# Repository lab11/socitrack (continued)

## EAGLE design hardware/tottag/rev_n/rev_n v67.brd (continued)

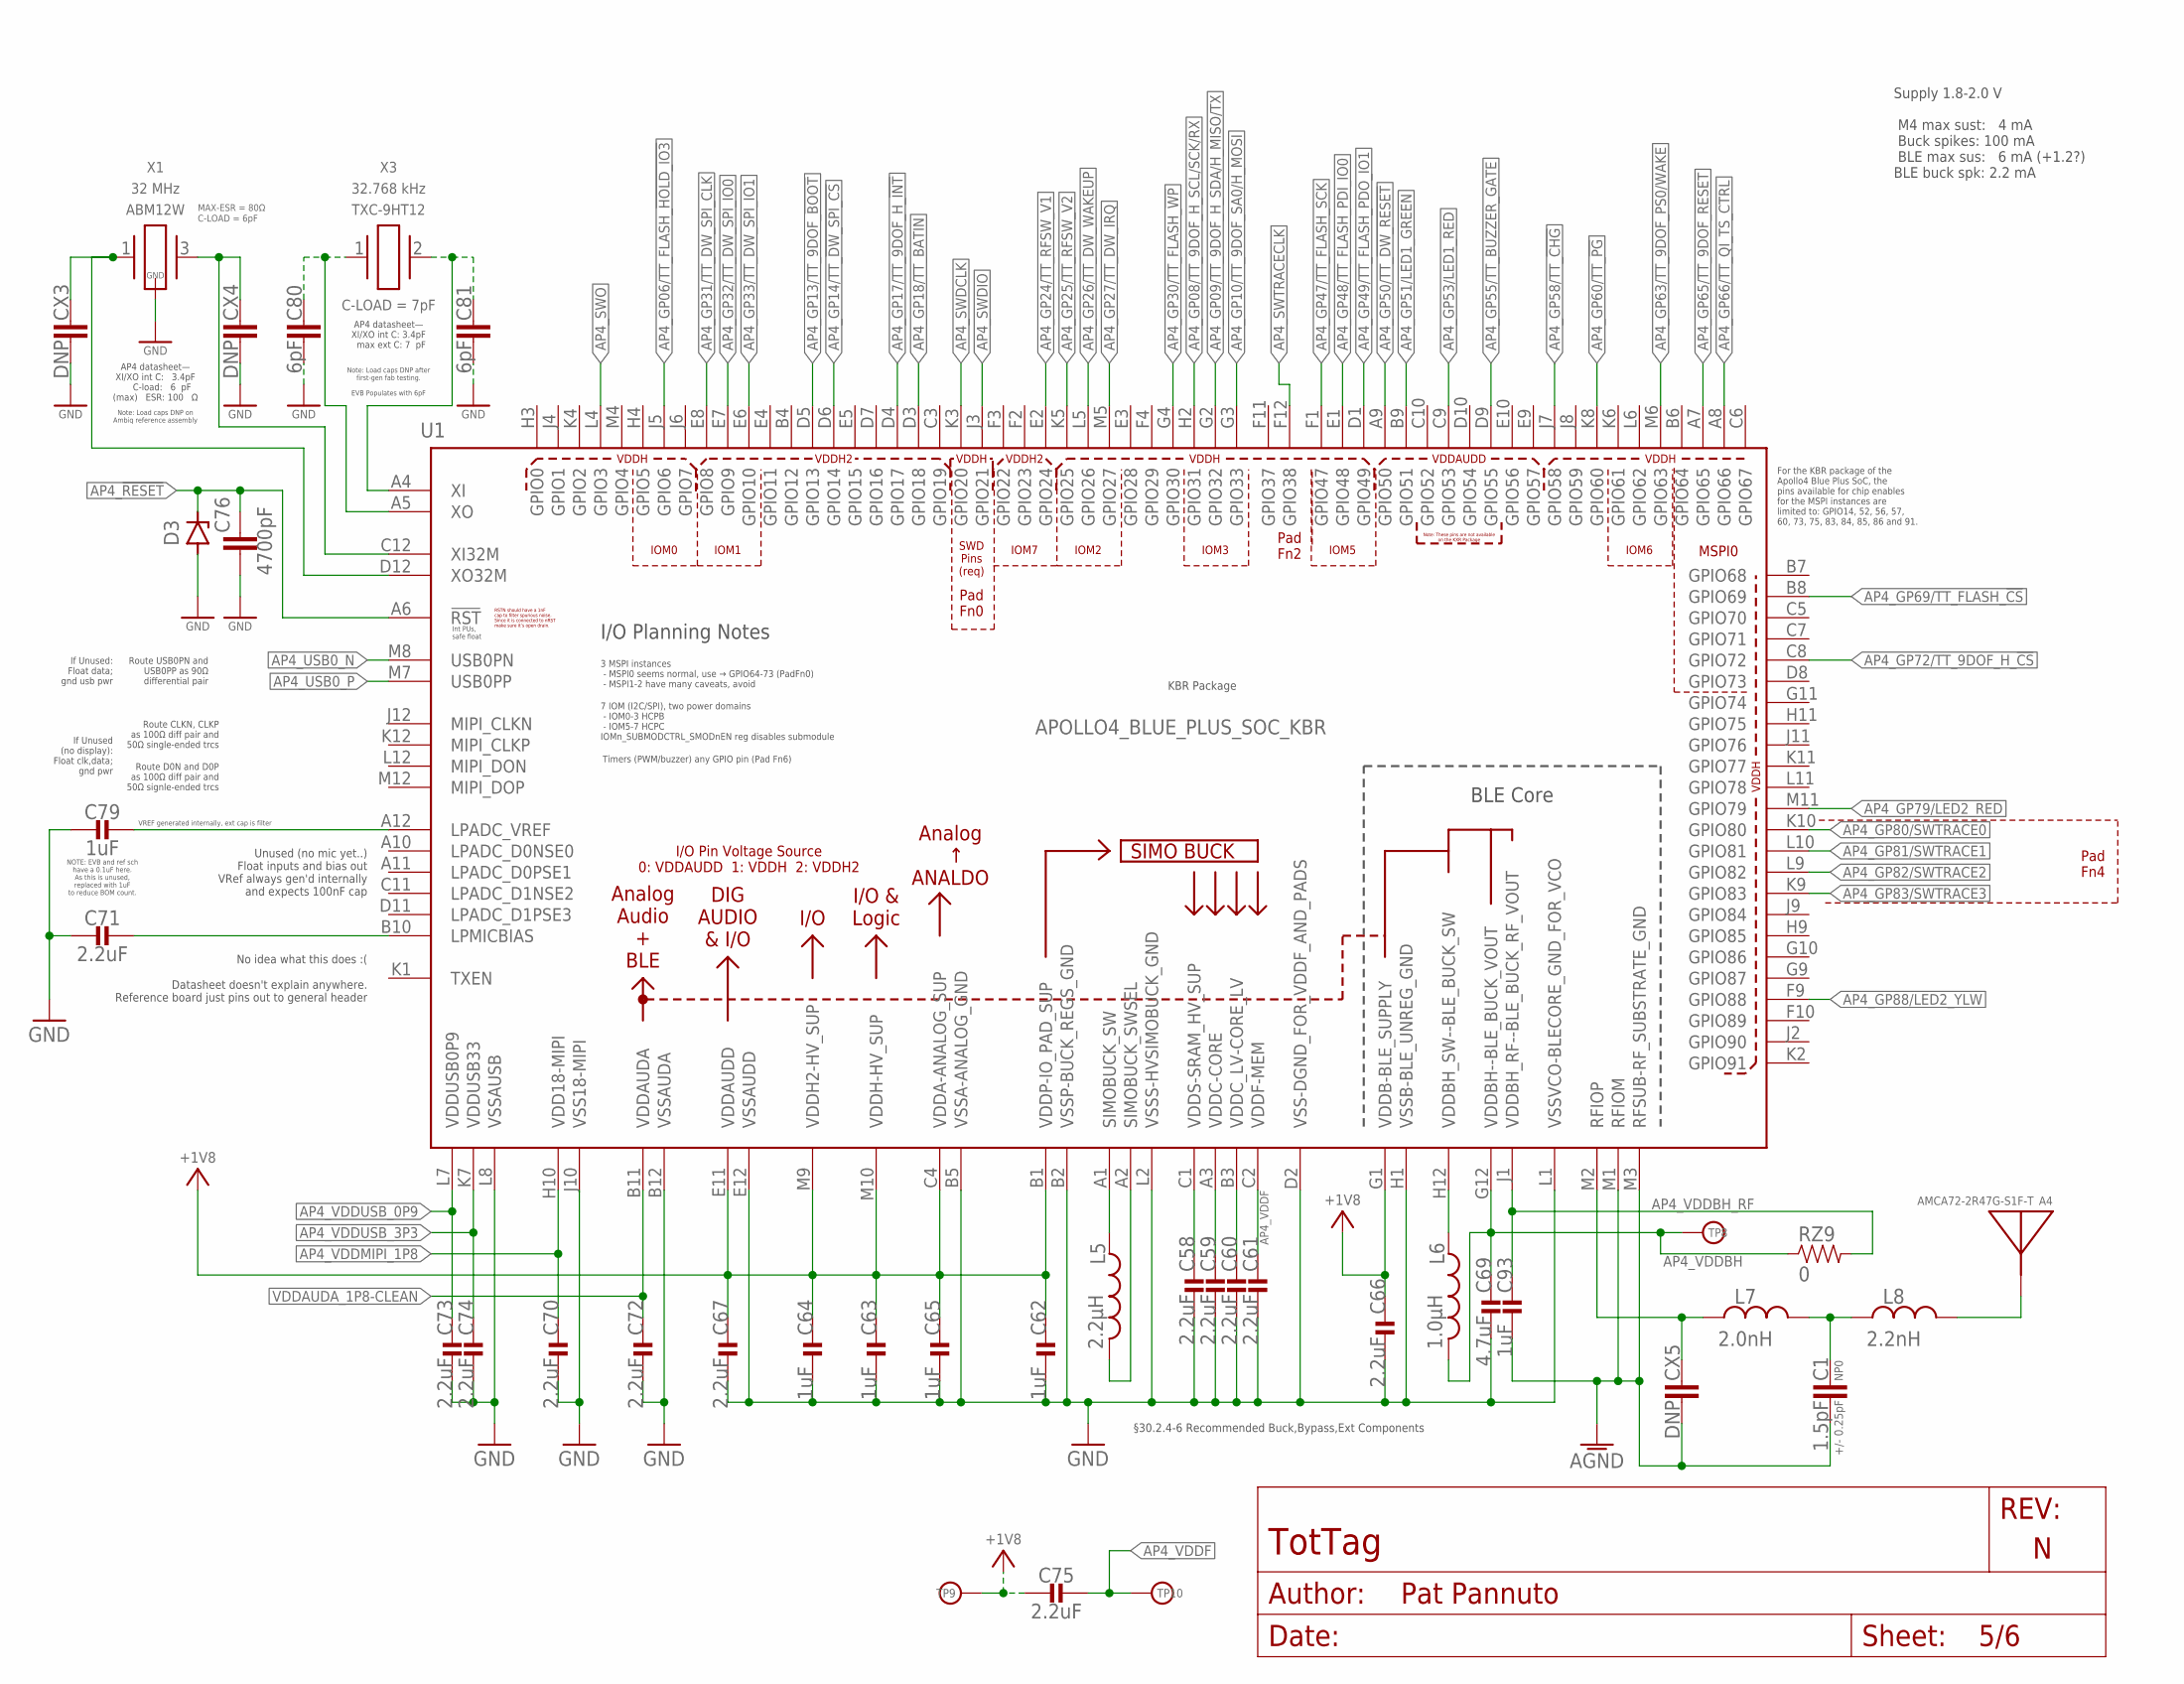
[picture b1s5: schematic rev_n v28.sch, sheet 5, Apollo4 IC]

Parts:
A4: AMCA72-2R47G-S1F-T; AMCA72-2R470G-S1F-T
C1: 1.5pF; CAPC1005X60; TOLERANCE +/- 0.25pF; MPN C0402C159C5GAC7867
C58, C59, C60, C61, C66, C67, C70, C71, C72, C73, C74, C75: 2.2uF; 0201_CAP; MPN GRM033R61A225KE47D
C62, C63, C64, C65, C79, C93: 1uF; 0201_CAP; MPN GRM033R61A105ME44D
C69: 4.7uF; 0402_CAP; MPN CL05A475MP5NRNC
C76: 4700pF; CAPC1005X60; MPN KGM05AR71E472KH
C80, C81: 6pF; CAPC1005X60; MPN GCM1555C1H6R0BA16D
CX3, CX4, CX5: DNP; CAPC1005X60
D3: ZENER; SODFL1608X70; MPN PESD5V0X1UB,135
L5: 2.2µH; 0805_CAP; MPN DFE201210U-2R2M=P2
L6: 1.0µH; 0603_CAP; MPN DFE18SAN1R0ME0L
L7: 2.0nH; INDC1006X60N; TOLERANCE +/- 0.1 nH; MPN CTTF0402F-2N0B
L8: 2.2nH; INDC1006X60N; TOLERANCE +/- 0.1 nH; MPN CTTF0402F-2N2B
RZ9: 0; 0402_RES; MPN RMCF0402ZT0R00
TP8: VDDBH; PAD.03X.03
TP9: VDDP; PAD.03X.03
TP10: VDDF; PAD.03X.03
U1: APOLLO4_BLUE_PLUS_SOC_KBR; APOLLO4_BLUE_SOC_BGA
X1: ABM12W; MPN ABM12W-32.0000MHZ-6-D1X-T3
X3: TXC-9HT12; MPN 9HT12-32.768KDZY-T

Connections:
AGND: C1.2, C93.P$2 (2), CX5.2, U1.M1 (RFIOM), U1.M3 (RFSUB-RF_SUBSTRATE_GND)
AP4_!RESET: C76.1, D3.1 (C), U1.A6 (!RST); also elsewhere on the board
AP4_GP06/TT_FLASH_!HOLD_IO3: U1.J5 (GPIO6); also elsewhere on the board
AP4_GP08/TT_9DOF_H_SCL/SCK/RX: U1.H2 (GPIO31); also elsewhere on the board
AP4_GP13/TT_9DOF_!BOOT: U1.D5 (GPIO13); also elsewhere on the board
AP4_GP14/TT_!DW_SPI_CS: U1.D6 (GPIO14); also elsewhere on the board
AP4_GP17/TT_9DOF_H_!INT: U1.D4 (GPIO17); also elsewhere on the board
AP4_GP18/TT_BATIN: U1.D3 (GPIO18); also elsewhere on the board
AP4_GP24/TT_RFSW_V1: U1.E2 (GPIO24); also elsewhere on the board
AP4_GP25/TT_RFSW_V2: U1.K5 (GPIO25); also elsewhere on the board
AP4_GP26/TT_DW_WAKEUP: U1.L5 (GPIO26); also elsewhere on the board
AP4_GP27/TT_DW_IRQ: U1.M5 (GPIO27); also elsewhere on the board
AP4_GP30/TT_FLASH_!WP: U1.G4 (GPIO30); also elsewhere on the board
AP4_GP31/TT_DW_SPI_CLK: U1.E8 (GPIO8); also elsewhere on the board
AP4_GP32/TT_DW_SPI_IO0: U1.E7 (GPIO9); also elsewhere on the board
AP4_GP33/TT_DW_SPI_IO1: U1.E6 (GPIO10); also elsewhere on the board
AP4_GP47/TT_FLASH_SCK: U1.F1 (GPIO47); also elsewhere on the board
AP4_GP48/TT_FLASH_PDI_IO0: U1.E1 (GPIO48); also elsewhere on the board
AP4_GP49/TT_FLASH_PDO_IO1: U1.D1 (GPIO49); also elsewhere on the board
AP4_GP50/TT_!DW_RESET: U1.A9 (GPIO50); also elsewhere on the board
AP4_GP51/LED1_GREEN: U1.B9 (GPIO51); also elsewhere on the board
AP4_GP53/LED1_RED: U1.C9 (GPIO53); also elsewhere on the board
AP4_GP55/TT_BUZZER_GATE: U1.D9 (GPIO55); also elsewhere on the board
AP4_GP58/TT_!CHG: U1.J7 (GPIO58); also elsewhere on the board
AP4_GP60/TT_!PG: U1.K8 (GPIO60); also elsewhere on the board
AP4_GP63/TT_9DOF_PS0/WAKE: U1.M6 (GPIO63); also elsewhere on the board
AP4_GP65/TT_9DOF_!RESET: U1.A7 (GPIO65); also elsewhere on the board
AP4_GP66/TT_QI_TS_CTRL: U1.A8 (GPIO66); also elsewhere on the board
AP4_GP69/TT_FLASH_!CS: U1.B8 (GPIO69); also elsewhere on the board
AP4_GP72/TT_9DOF_H_!CS: U1.C8 (GPIO72); also elsewhere on the board
AP4_GP79/LED2_RED: U1.M11 (GPIO79); also elsewhere on the board
AP4_GP88/LED2_YLW: U1.F9 (GPIO88); also elsewhere on the board
AP4_LPADC_VREF: C79.P$2 (2), U1.A12 (LPADC_VREF)
AP4_LPMICBIAS: C71.P$2 (2), U1.B10 (LPMICBIAS)
AP4_RFIOP1: CX5.1, L7.1, U1.M2 (RFIOP)
AP4_SWDCLK: U1.K3 (GPIO20); also elsewhere on the board
AP4_SWDIO: U1.J3 (GPIO21); also elsewhere on the board
AP4_SWO: U1.L4 (GPIO3); also elsewhere on the board
AP4_USB0_N: U1.M8 (USB0PN)
AP4_USB0_P: U1.M7 (USB0PP)
AP4_VDDBH: C69.1, L6.2, RZ9.1, TP8.P$1, U1.G12 (VDDBH--BLE_BUCK_VOUT)
AP4_VDDBH_RF: C93.P$1 (1), RZ9.2, U1.J1 (VDDBH_RF--BLE_BUCK_RF_VOUT)
AP4_VDDBH_SW: L6.1, U1.H12 (VDDBH_SW--BLE_BUCK_SW)
AP4_VDDC: C59.P$1 (1), U1.A3 (VDDC-CORE)
AP4_VDDC_LV: C60.P$1 (1), U1.B3 (VDDC_LV-CORE_LV)
AP4_VDDF: C61.P$1 (1), C75.P$1 (1), TP10.P$1, U1.C2 (VDDF-MEM)
AP4_VDDMIPI_1P8: C70.P$1 (1), U1.H10 (VDD18-MIPI); also elsewhere on the board
AP4_VDDS: C58.P$1 (1), U1.C1 (VDDS-SRAM_HV_SUP)
AP4_VDDUSB_0P9: C73.P$1 (1), U1.L7 (VDDUSB0P9); also elsewhere on the board
AP4_VDDUSB_3P3: C74.P$1 (1), U1.K7 (VDDUSB33); also elsewhere on the board
AP4_XI: C81.1, U1.A4 (XI), X3.2
AP4_XI32M: CX4.1, U1.C12 (XI32M), X1.3 (2)
AP4_XO: C80.1, U1.A5 (XO), X3.1
AP4_XO32M: CX3.1, U1.D12 (XO32M), X1.1
BLE_RFOUT: A4.S1, L8.2
GND: C58.P$2 (2), C59.P$2 (2), C60.P$2 (2), C61.P$2 (2), C62.P$2 (2), C63.P$2 (2), C64.P$2 (2), C65.P$2 (2), C66.P$2 (2), C67.P$2 (2), C69.2, C70.P$2 (2), C71.P$1 (1), C72.P$2 (2), C73.P$2 (2), C74.P$2 (2), C76.2, C79.P$1 (1), C80.2, C81.2, CX3.2, CX4.2, D3.2 (A), U1.B2 (VSSP-BUCK_REGS_GND), U1.B5 (VSSA-ANALOG_GND), U1.B12 (VSSAUDA), U1.D2 (VSS-DGND_FOR_VDDF_AND_PADS), U1.E12 (VSSAUDD), U1.H1 (VSSB-BLE_UNREG_GND), U1.J10 (VSS18-MIPI), U1.L1 (VSSVCO-BLECORE_GND_FOR_VCO), U1.L2 (VSSS-HVSIMOBUCK_GND), U1.L8 (VSSAUSB), X1.2 (GND), X1.4 (GND); also elsewhere on the board
unnamed: C1.1, L7.2, L8.1
SIMOBUCK_SW: L5.P$1 (1), U1.A1 (SIMOBUCK_SW)
SIMOBUCK_SWSEL: L5.P$2 (2), U1.A2 (SIMOBUCK_SWSEL)
VDDAUDA_1P8-CLEAN: C72.P$1 (1), U1.B11 (VDDAUDA); also elsewhere on the board

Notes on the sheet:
Supply 1.8-2.0 V M4 max sust: 4 mA Buck spikes: 100 mA BLE max sus: 6 mA (+1.2?) BLE buck spk: 2.2 mA
Note: Load caps DNP on Ambiq reference assembly
Int PUs, safe float
If Unused: Float data; gnd usb pwr
If Unused (no display): Float clk,data; gnd pwr
Unused (no mic yet..) Float inputs and bias out VRef always gen'd internally and expects 100nF cap
No idea what this does :( Datasheet doesn't explain anywhere. Reference board just pins out to general header
I/O Planning Notes
3 MSPI instances - MSPI0 seems normal, use → GPIO64-73 (PadFn0) - MSPI1-2 have many caveats, avoid
7 IOM (I2C/SPI), two power domains - IOM0-3 HCPB - IOM5-7 HCPC IOMn_SUBMODCTRL_SMODnEN reg disables submodule
MSPI0
IOM0
IOM1
Timers (PWM/buzzer) any GPIO pin (Pad Fn6)
KBR Package
For the KBR package of the Apollo4 Blue Plus SoC, the pins available for chip enables for the MSPI instances are limited to: GPIO14, 52, 56, 57, 60, 73, 75, 83, 84, 85, 86 and 91.
§30.2.4-6 Recommended Buck,Bypass,Ext Components
SWD Pins (req)
VREF generated internally, ext cap is filter
IOM3
AP4 datasheet— XI/XO int C: 3.4pF max ext C: 7 pF
AP4 datasheet— XI/XO int C: 3.4pF C-load: 6 pF (max) ESR: 100 Ω
Pad Fn4
Pad Fn2
Pad Fn0
Note: Load caps DNP after first-gen fab testing. EVB Populates with 6pF
Route USB0PN and USB0PP as 90Ω differential pair
Route CLKN, CLKP as 100Ω diff pair and 50Ω single-ended trcs
Route D0N and D0P as 100Ω diff pair and 50Ω signle-ended trcs
NOTE: EVB and ref sch have a 0.1uF here. As this is unused, replaced with 1uF to reduce BOM count.
IOM2
IOM5
IOM6
IOM7

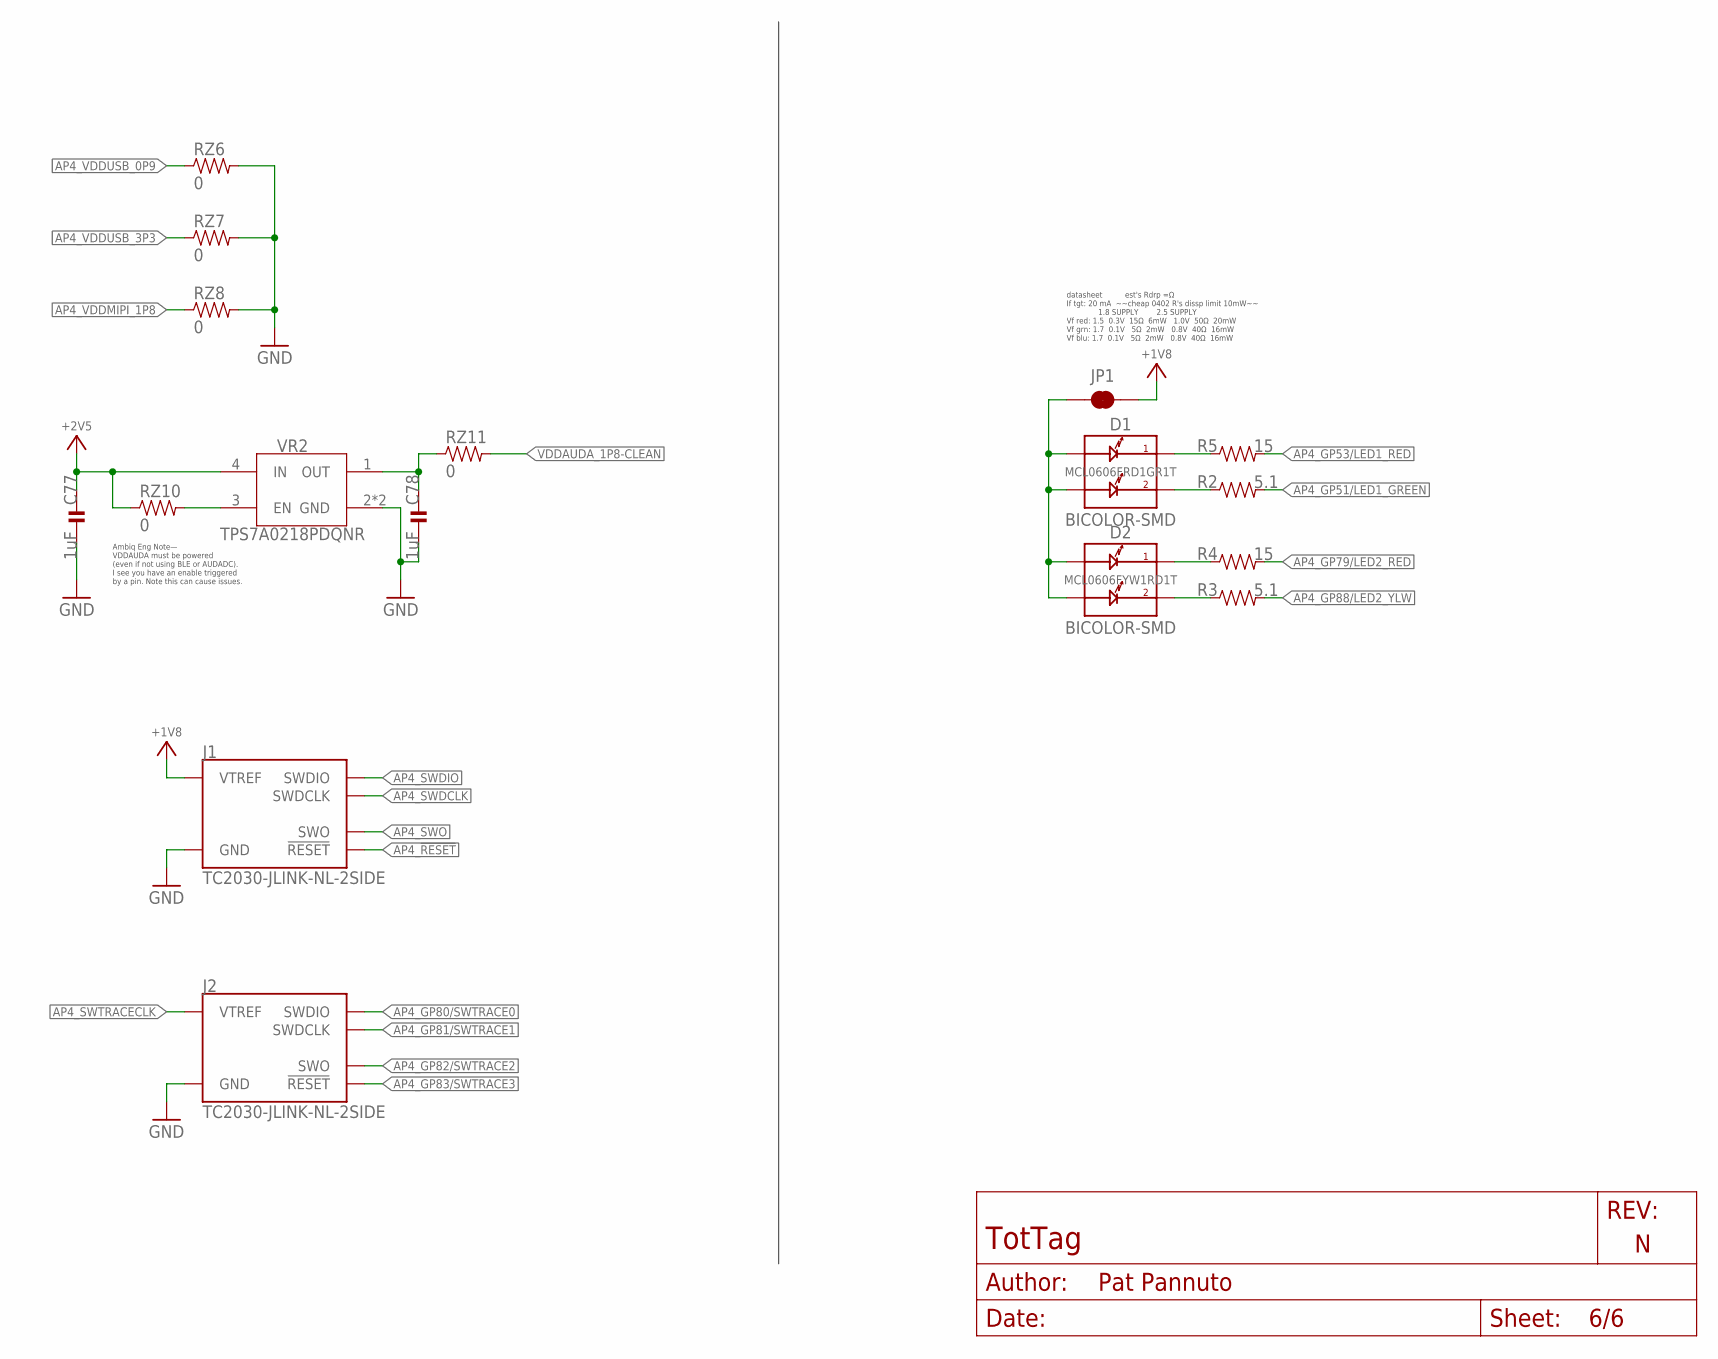
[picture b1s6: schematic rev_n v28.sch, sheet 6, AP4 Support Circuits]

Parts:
C77, C78: 1uF; 0201_CAP; MPN GRM033R61A105ME44D
D1: BICOLOR-SMD; LED-0606; MPN MCL0606FRD1GR1T
D2: BICOLOR-SMD; LED-0606; MPN MCL0606FYW1RD1T
J1, J2: TC2030-JLINK-NL-2SIDE; TC2030-IDC-NL-2SIDE
JP1: JUMPER-SMT_2_NC_TRACE_SILK; SMT-JUMPER_2_NC_TRACE_SILK
R2, R3: 5.1; 0402_RES; MPN RC0402JR-075R1L
R4, R5: 15; 0402_RES; MPN RC0402JR-0715RL
RZ6, RZ7, RZ8, RZ10, RZ11: 0; 0402_RES; MPN RMCF0402ZT0R00
VR2: TPS7A0218PDQNR; 4-XDFN-EP

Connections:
+2V5: C77.P$1 (1), RZ10.1, VR2.4 (IN); also elsewhere on the board
AP4_!RESET: J1.3 (!RESET), J1.B3 (!RESET); also elsewhere on the board
AP4_GP51/LED1_GREEN: R2.2; also elsewhere on the board
AP4_GP53/LED1_RED: R5.2; also elsewhere on the board
AP4_GP79/LED2_RED: R4.2; also elsewhere on the board
AP4_GP88/LED2_YLW: R3.2; also elsewhere on the board
AP4_LED2_BLUE_COMM: D1.C1, R5.1
AP4_LED_BLUE_COMM: D2.C2, R3.1
AP4_LED_GREEN_COMM: D2.C1, R4.1
AP4_LED_RED_COMM: D1.C2, R2.1
AP4_SWDCLK: J1.4 (SWDCLK), J1.B4 (SWDCLK); also elsewhere on the board
AP4_SWDIO: J1.2 (SWDIO), J1.B2 (SWDIO); also elsewhere on the board
AP4_SWO: J1.6 (SWO), J1.B6 (SWO); also elsewhere on the board
AP4_VDDMIPI_1P8: RZ8.1; also elsewhere on the board
AP4_VDDUSB_0P9: RZ6.1; also elsewhere on the board
AP4_VDDUSB_3P3: RZ7.1; also elsewhere on the board
GND: C77.P$2 (2), C78.P$2 (2), J1.5 (GND), J1.B5 (GND), J2.5 (GND), J2.B5 (GND), RZ6.2, RZ7.2, RZ8.2, VR2.2 (GND), VR2.PAD (GND); also elsewhere on the board
LED_SUP: D1.A1, D1.A2, D2.A1, D2.A2, JP1.1; also elsewhere on the board
VDDAUDA_1P8-CLEAN: RZ11.2; also elsewhere on the board
VR2_EN: RZ10.2, VR2.3 (EN)
VR2_OUT: C78.P$1 (1), RZ11.1, VR2.1 (OUT)

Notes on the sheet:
Ambiq Eng Note— VDDAUDA must be powered (even if not using BLE or AUDADC). I see you have an enable triggered by a pin. Note this can cause issues.
datasheet est's Rdrp =Ω If tgt: 20 mA ~~cheap 0402 R's dissp limit 10mW~~ 1.8 SUPPLY 2.5 SUPPLY Vf red: 1.5 0.3V 15Ω 6mW 1.0V 50Ω 20mW Vf grn: 1.7 0.1V 5Ω 2mW 0.8V 40Ω 16mW Vf blu: 1.7 0.1V 5Ω 2mW 0.8V 40Ω 16mW

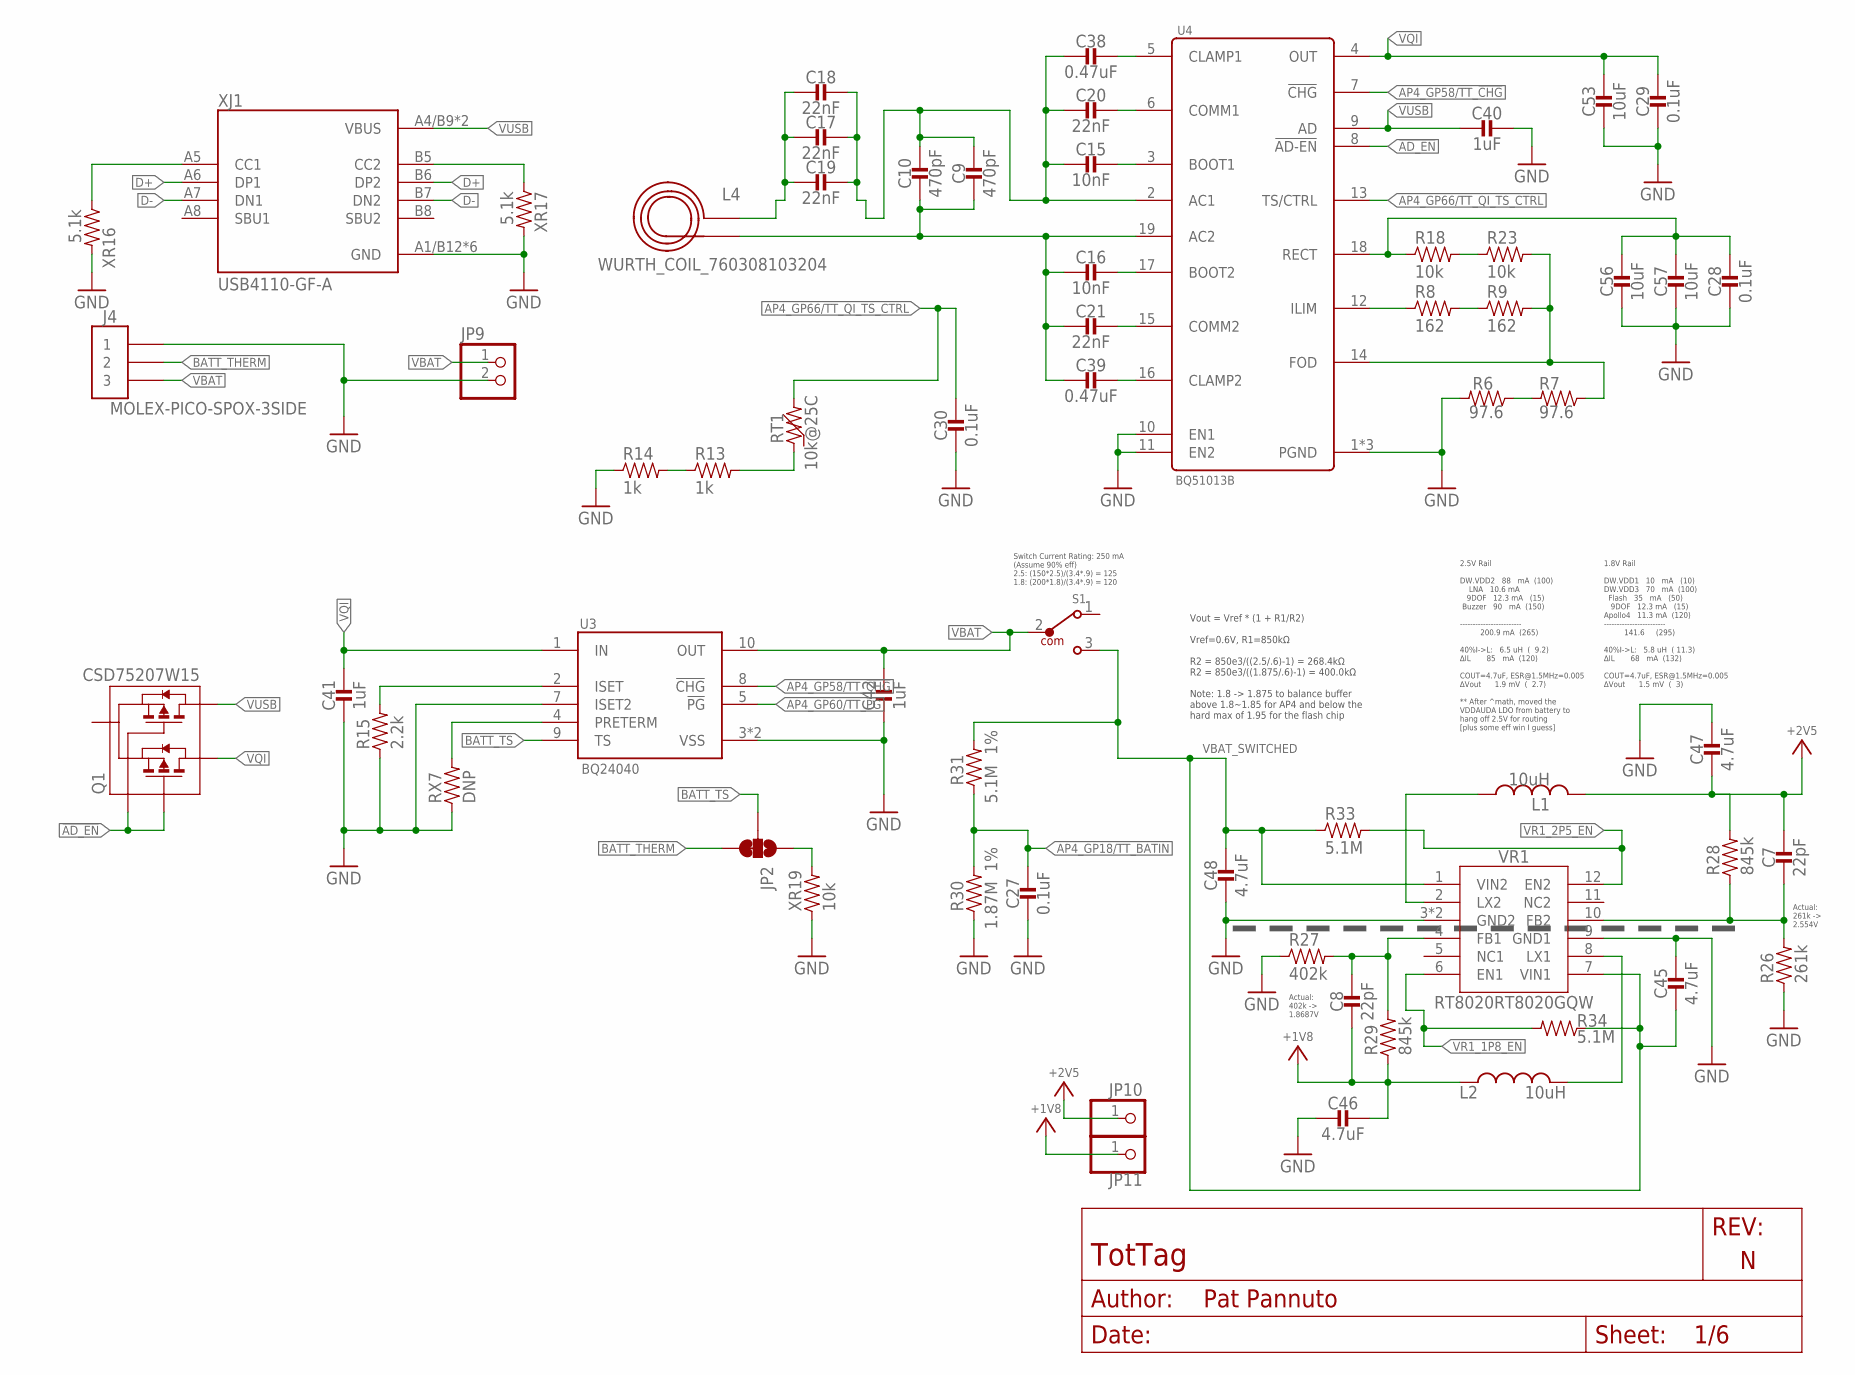
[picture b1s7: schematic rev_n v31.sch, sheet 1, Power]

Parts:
C7, C8: 22pF; 0201_CAP; MPN GRM0335C1H220FA01D
C9, C10: 470pF; 0402_CAP; MPN GRM1555C1H471JA01J; DIGIKEY 490-6242-1-ND
C15, C16: 10nF; 0402_CAP; MPN GRM155R71H103KA88J; DIGIKEY 490-6351-2-ND
C17, C18, C19: 22nF; 0402_CAP; MPN GRM155R71E223JA61D; DIGIKEY 490-10699-2-ND
C20, C21: 22nF; 0402_CAP; MPN CC0402ZRY5V8BB223; DIGIKEY 311-3823-1-ND
C27, C28, C29, C30: 0.1uF; 0402_CAP; MPN GRM155R71C104KA88J; DIGIKEY 490-6328-1-ND
C38, C39: 0.47uF; 0402_CAP; MPN GRT155R61E474ME01D; DIGIKEY 490-12270-1-ND
C40, C41, C42: 1uF; 0402_CAP; MPN GRM155R70J105KA12J
C45, C46, C47, C48: 4.7uF; 0603_CAP; MPN C1608X7S1A475K080AC
C53, C56, C57: 10uF; 0603_CAP; MPN CM105X5R106M25AT; DIGIKEY 1253-CM105X5R106M25ATCT-ND
J4: MOLEX-PICO-SPOX-3SIDE; MOLEX-PICO-SPOX-3_SIDE
JP2: JUMPER-SMT_3_1-NC_TRACE_SILK; SMT-JUMPER_3_1-NC_TRACE_SILK
JP9: PINHD-1X2; 1X02
JP10, JP11: PINHD-1X1; 1X01
L1, L2: 10uH; NRX3015; MPN NR3015T100M
L4: WURTH_COIL_760308103204
Q1: CSD75207W15; DSBGA
R6, R7: 97.6; 0402_RES; MPN RMCF0402FT97R6; DIGIKEY RMCF0402FT97R6CT-ND
R8, R9: 162; 0402_RES; MPN RMCF0402FT162R; DIGIKEY RMCF0402FT162RCT-ND
R13, R14: 1k; 0402_RES
R15: 2.2k; 0402_RES; MPN RMCF0402JT2K20; DIGIKEY RMCF0402JT2K20CT-ND
R18, R23: 10k; 0402_RES; MPN RC0402JR-0710KL; DIGIKEY 311-10KJRCT-ND
R26: 261k; 0201_RES; MPN ERJ-1GNF2613C
R27: 402k; 0201_RES; MPN ERJ-1GNF4023C
R28, R29: 845k; 0201_RES; MPN ERJ-1GNF8453C
R30: 1.87M; 0402_RES; TOLERANCE 1%; MPN RMCF0402FT1M87
R31: 5.1M; 0402_RES; TOLERANCE 1%; MPN RMCF0402FT5M10; DIGIKEY RMCF0402FT5M10CT-ND
R33, R34: 5.1M; 0402_RES; MPN RMCF0402FT5M10; DIGIKEY RMCF0402FT5M10CT-ND
RT1: 10k@25C; 0402_RES; MPN NCU15XH103F60RC; DIGIKEY 490-18149-1-ND
RX7: DNP; 0402_RES
S1: 450404015514; DIGIKEY 732-13665-1-ND
U3: BQ24040; DSQ0010A
U4: BQ51013B; RHL0020A
VR1: RT8020RT8020GQW; SON45P300X300X80-13T160X250N
XJ1: USB4110-GF-A; GCT_USB4110-GF-A
XR16, XR17: 5.1k; 0402_RES; MPN RMCF0402FT5K10; DIGIKEY RMCF0402FT5K10CT-ND
XR19: 10k; 0402_RES; MPN RC0402JR-0710KL; DIGIKEY 311-10KJRCT-ND

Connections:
!AD_EN: Q1.A1 (G1), Q1.C1 (G2), U4.8 (!AD-EN)
+2V5: C7.P$1 (1), C47.2, JP10.1, L1.P$2 (2), R28.2; also elsewhere on the board
AP4_GP18/TT_BATIN: C27.1, R30.2, R31.1; also elsewhere on the board
AP4_GP58/TT_!CHG: U3.8 (!CHG), U4.7 (!CHG); also elsewhere on the board
AP4_GP60/TT_!PG: U3.5 (!PG); also elsewhere on the board
AP4_GP66/TT_QI_TS_CTRL: C30.1, RT1.2, U4.13 (TS/CTRL); also elsewhere on the board
BATT_THERM: J4.2, J4.2SUPP (2), JP2.3; also elsewhere on the board
BATT_TS: JP2.2, U3.9 (TS); also elsewhere on the board
BQ_AC1: C9.1, C10.1, C15.2, C17.1, C18.1, C19.1, C20.2, C38.2, U4.2 (AC1)
BQ_AC2: C9.2, C10.2, C16.2, C21.2, C39.2, L4.P$2 (2), U4.19 (AC2)
BQ_BOOT1: C15.1, U4.3 (BOOT1)
BQ_BOOT2: C16.1, U4.17 (BOOT2)
BQ_CLAMP1: C38.1, U4.5 (CLAMP1)
BQ_CLAMP2: C39.1, U4.16 (CLAMP2)
BQ_COMM1: C20.1, U4.6 (COMM1)
BQ_COMM2: C21.1, U4.15 (COMM2)
BQ_FOD: R7.1, R9.2, R23.2, U4.14 (FOD)
BQ_ILM: R8.1, U4.12 (ILIM)
BQ_ISET: R15.2, U3.2 (ISET)
BQ_RECT: C28.1, C56.1, C57.1, R18.1, U4.18 (RECT)
COIL_AC1: C17.2, C18.2, C19.2, L4.P$1 (1)
D+: XJ1.A6 (DP1), XJ1.B6 (DP2)
D-: XJ1.A7 (DN1), XJ1.B7 (DN2)
GND: C27.2, C28.2, C29.2, C30.2, C40.1, C41.2, C42.2, C45.1, C46.2, C47.1, C48.2, C53.2, C56.2, C57.2, J4.1, J4.1SUPP (1), JP9.2, R6.2, R14.1, R15.1, R26.1, R27.1, R30.1, RX7.1, U3.3 (VSS), U3.7 (ISET2), U3.PAD (VSS), U4.1 (PGND), U4.10 (EN1), U4.11 (EN2), U4.20 (PGND), U4.PAD (PGND), VR1.3 (GND2), VR1.9 (GND1), VR1.13 (GND2), XJ1.A1/B12 (GND), XJ1.B1/A12 (GND), XJ1.S1 (GND), XJ1.S2 (GND), XJ1.S3 (GND), XJ1.S4 (GND), XR16.2, XR17.2, XR19.1; also elsewhere on the board
unnamed: R6.1, R7.2
unnamed 122: JP2.1, XR19.2; also elsewhere on the board
unnamed: RX7.2, U3.4 (PRETERM)
unnamed: R18.2, R23.1
unnamed: R8.2, R9.1
unnamed: R13.2, RT1.1
unnamed 127: R13.1, R14.2; also elsewhere on the board
VBAT: C42.1, J4.3, J4.3SUPP (3), JP9.1, S1.2, U3.10 (OUT); also elsewhere on the board
VBAT_SWITCHED: C45.2, C48.1, R31.2, R33.1, R34.1, S1.3, VR1.1 (VIN2), VR1.7 (VIN1)
VQI: C29.1, C41.1, C53.1, Q1.A2 (D1), Q1.A3 (D1), Q1.B3 (D1), U3.1 (IN), U4.4 (OUT)
VR1_1P8_EN: R34.2, VR1.6 (EN1)
VR1_2P5_EN: R33.2, VR1.12 (EN2)
VR1_FB1: C8.P$1 (1), R27.2, R29.2, VR1.4 (FB1)
VR1_FB2: C7.P$2 (2), R26.2, R28.1, VR1.10 (FB2)
VR1_LX1: L2.P$2 (2), VR1.8 (LX1)
VR1_LX2: L1.P$1 (1), VR1.2 (LX2)
VUSB: C40.2, Q1.B2 (D2), Q1.C2 (D2), Q1.C3 (D2), U4.9 (AD), XJ1.A4/B9 (VBUS), XJ1.B4/A9 (VBUS)

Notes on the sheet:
2.5V Rail DW.VDD2 88 mA (100) LNA 10.6 mA 9DOF 12.3 mA (15) Buzzer 90 mA (150) ------------------------ 200.9 mA (265) 40%I->L: 6.5 uH ( 9.2) ∆IL 85 mA (120) COUT=4.7uF, ESR@1.5MHz=0.005 ∆Vout 1.9 mV ( 2.7) ** After ^math, moved the VDDAUDA LDO from battery to hang off 2.5V for routing [plus some e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
1.8V Rail DW.VDD1 10 mA (10) DW.VDD3 70 mA (100) Flash 35 mA (50) 9DOF 12.3 mA (15) Apollo4 11.3 mA (120) ------------------------ 141.6 (295) 40%I->L: 5.8 uH ( 11.3) ∆IL 68 mA (132) COUT=4.7uF, ESR@1.5MHz=0.005 ∆Vout 1.5 mV ( 3)
Vout = Vref * (1 + R1/R2) Vref=0.6V, R1=850kΩ R2 = 850e3/((2.5/.6)-1) = 268.4kΩ R2 = 850e3/((1.875/.6)-1) = 400.0kΩ Note: 1.8 -> 1.875 to balance buffer above 1.8~1.85 for AP4 and below the hard max of 1.95 for the flash chip
Switch Current Rating: 250 mA (Assume 90% eff) 2.5: (150*2.5)/(3.4*.9) = 125 1.8: (200*1.8)/(3.4*.9) = 120
Actual: 402k -> 1.8687V
Actual: 261k -> 2.554V

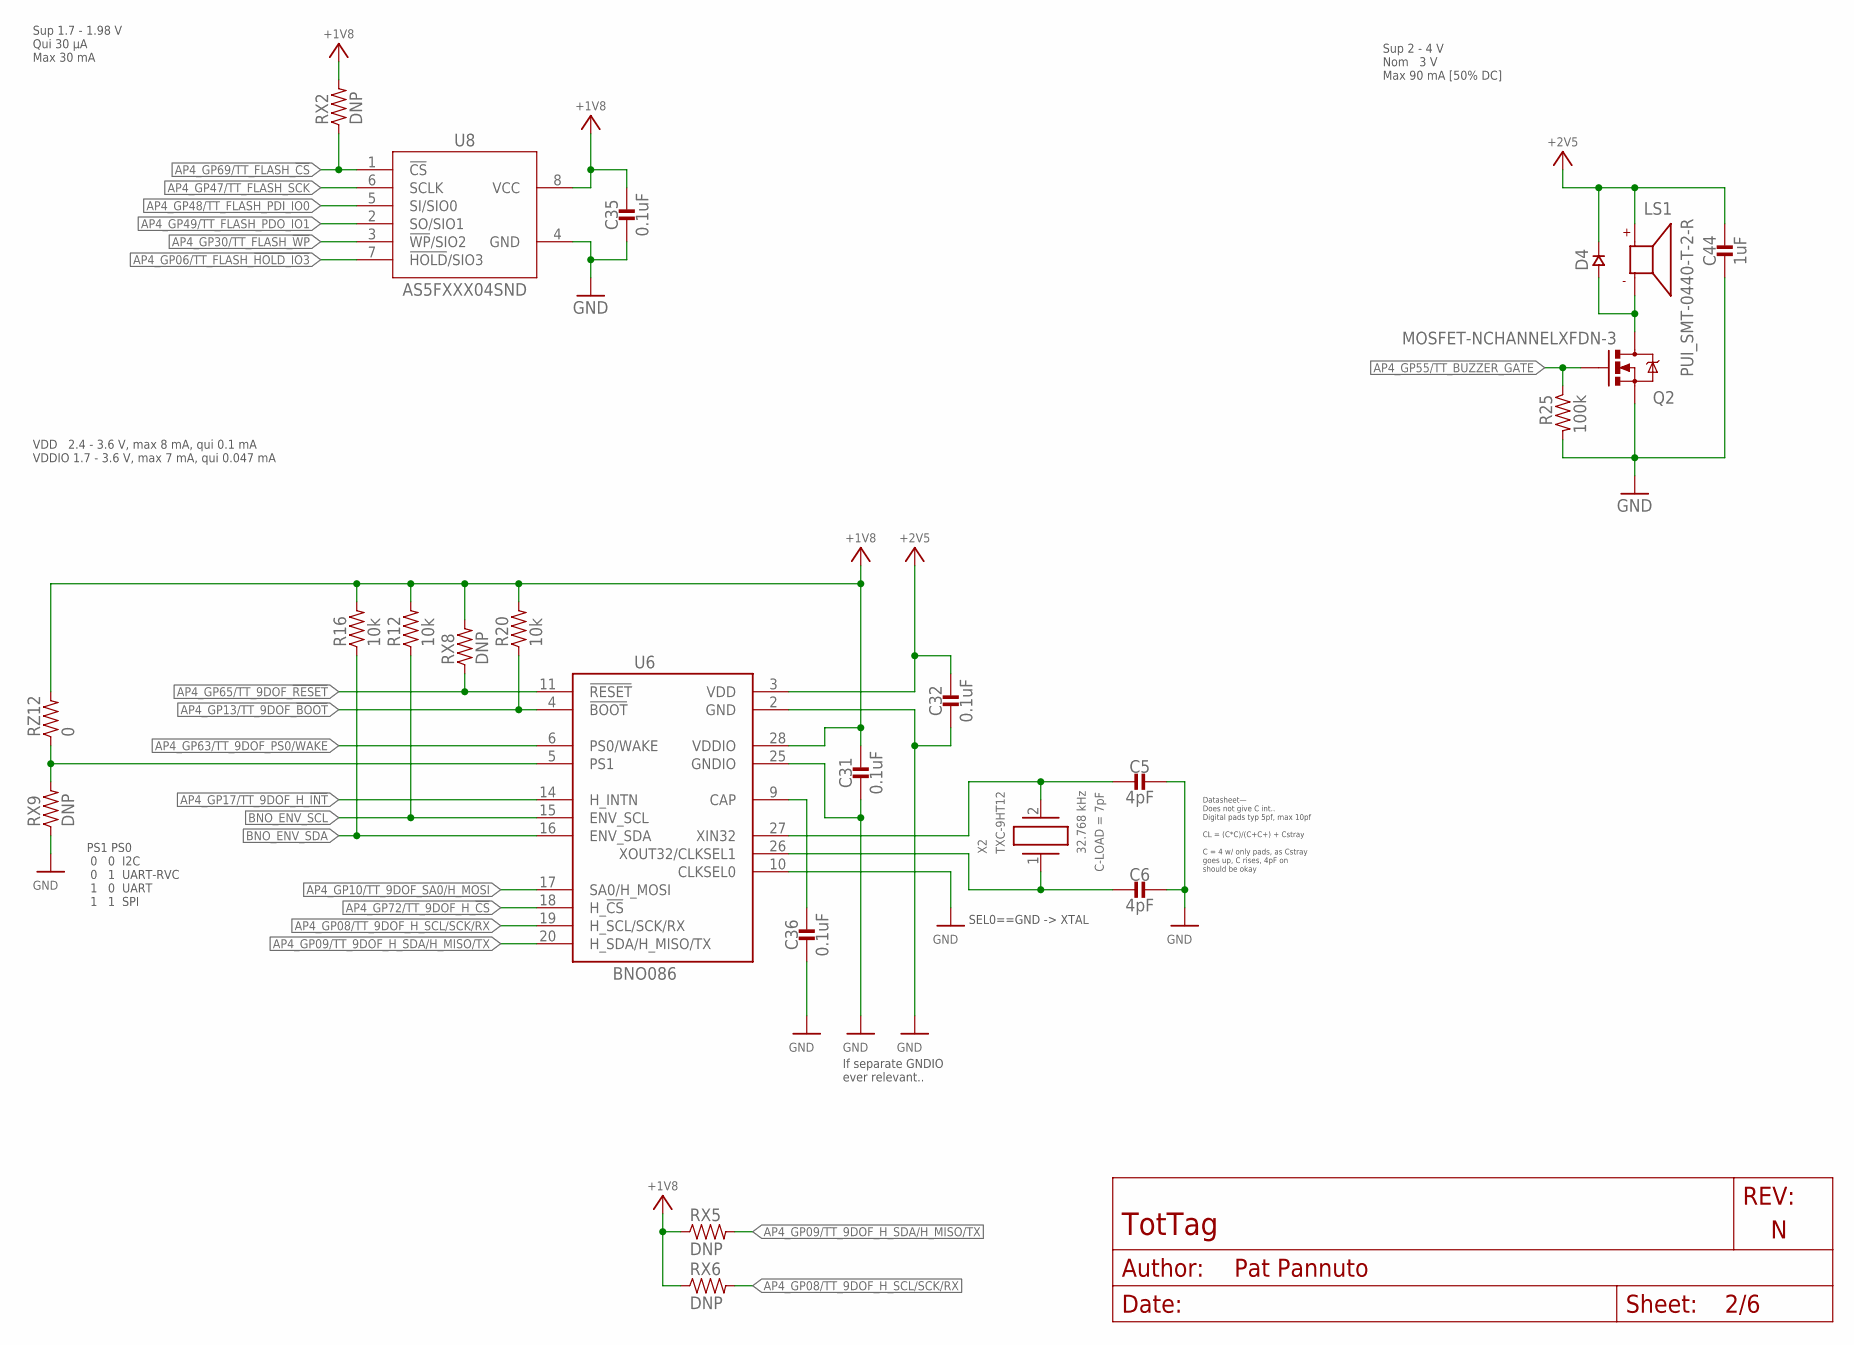
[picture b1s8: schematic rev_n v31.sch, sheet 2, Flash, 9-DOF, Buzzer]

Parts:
C5, C6: 4pF; 0201_CAP; MPN GRM0335C1H4R0BA01D
C31, C32, C35, C36: 0.1uF; 0402_CAP; MPN CL05A104KP5NNNC
C44: 1uF; 0402_CAP; MPN GRM155R70J105KA12J
D4: DIODE0402; 0402_DIODE; MPN CDSQR400B-HF; DIGIKEY 641-2087-1-ND
LS1: PUI_SMT-0440-T-2-R; SMT-0440-T-2-R
Q2: MOSFET-NCHANNELXFDN-3; XFDFN-3
R12, R16, R20: 10k; 0402_RES; MPN RC0402JR-0710KL; DIGIKEY 311-10KJRCT-ND
R25: 100k; 0402_RES; MPN RT0402BRE07100KL
RX2, RX5, RX6, RX8, RX9: DNP; 0603-RES
RZ12: 0; 0402_RES; MPN RMCF0402ZT0R00
U6: BNO086; LGA28R0P510X4_5P2X3P8X1
U8: AS5FXXX04SND; AS5FXXXXXXXX-XXLXN
X2: TXC-9HT12; MPN 9HT12-32.768KDZY-T

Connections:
9DOF_CAP: C36.1, U6.9 (CAP)
9DOF_XI: C5.P$2 (2), U6.27 (XIN32), X2.2
9DOF_XO: C6.P$2 (2), U6.26 (XOUT32/CLKSEL1), X2.1
+2V5: C32.1, C44.1, D4.CATHODE, LS1.+, U6.3 (VDD); also elsewhere on the board
AP4_GP06/TT_FLASH_!HOLD_IO3: U8.7 (!HOLD!/SIO3); also elsewhere on the board
AP4_GP08/TT_9DOF_H_SCL/SCK/RX: RX6.2, U6.19 (H_SCL/SCK/RX); also elsewhere on the board
AP4_GP13/TT_9DOF_!BOOT: R20.1, U6.4 (!BOOT); also elsewhere on the board
AP4_GP17/TT_9DOF_H_!INT: U6.14 (H_INTN); also elsewhere on the board
AP4_GP30/TT_FLASH_!WP: U8.3 (!WP!/SIO2); also elsewhere on the board
AP4_GP47/TT_FLASH_SCK: U8.6 (SCLK); also elsewhere on the board
AP4_GP48/TT_FLASH_PDI_IO0: U8.5 (SI/SIO0); also elsewhere on the board
AP4_GP49/TT_FLASH_PDO_IO1: U8.2 (SO/SIO1); also elsewhere on the board
AP4_GP55/TT_BUZZER_GATE: Q2.G, R25.1; also elsewhere on the board
AP4_GP63/TT_9DOF_PS0/WAKE: U6.6 (PS0/WAKE); also elsewhere on the board
AP4_GP65/TT_9DOF_!RESET: RX8.1, U6.11 (!RESET); also elsewhere on the board
AP4_GP69/TT_FLASH_!CS: RX2.1, U8.1 (!CS); also elsewhere on the board
AP4_GP72/TT_9DOF_H_!CS: U6.18 (H_!CS); also elsewhere on the board
BNO_ENV_SCL: R12.1, U6.15 (ENV_SCL)
BNO_ENV_SDA: R16.1, U6.16 (ENV_SDA)
BNO_PS1: RX9.2, RZ12.1, U6.5 (PS1); also elsewhere on the board
GND: C5.P$1 (1), C6.P$1 (1), C31.2, C32.2, C35.2, C36.2, C44.2, Q2.S, R25.2, RX9.1, U6.2 (GND), U6.10 (CLKSEL0), U6.25 (GNDIO), U8.4 (GND); also elsewhere on the board
unnamed: D4.ANODE, LS1.- (N), Q2.D

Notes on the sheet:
Sup 1.7 - 1.98 V Qui 30 µA Max 30 mA
VDD 2.4 - 3.6 V, max 8 mA, qui 0.1 mA VDDIO 1.7 - 3.6 V, max 7 mA, qui 0.047 mA
Sup 2 - 4 V Nom 3 V Max 90 mA [50% DC]
If separate GNDIO ever relevant..
Datasheet— Does not give C int.. Digital pads typ 5pf, max 10pf CL = (C*C)/(C+C+) + Cstray C = 4 w/ only pads, as Cstray goes up, C rises, 4pF on should be okay
SEL0==GND -> XTAL
PS1 PS0 0 0 I2C 0 1 UART-RVC 1 0 UART 1 1 SPI
